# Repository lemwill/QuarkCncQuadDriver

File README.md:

# QuarkCnc

Inspired from:
https://github.com/Expatria-Technologies/grblhal_2000_PrintNC

https://github.com/grblHAL

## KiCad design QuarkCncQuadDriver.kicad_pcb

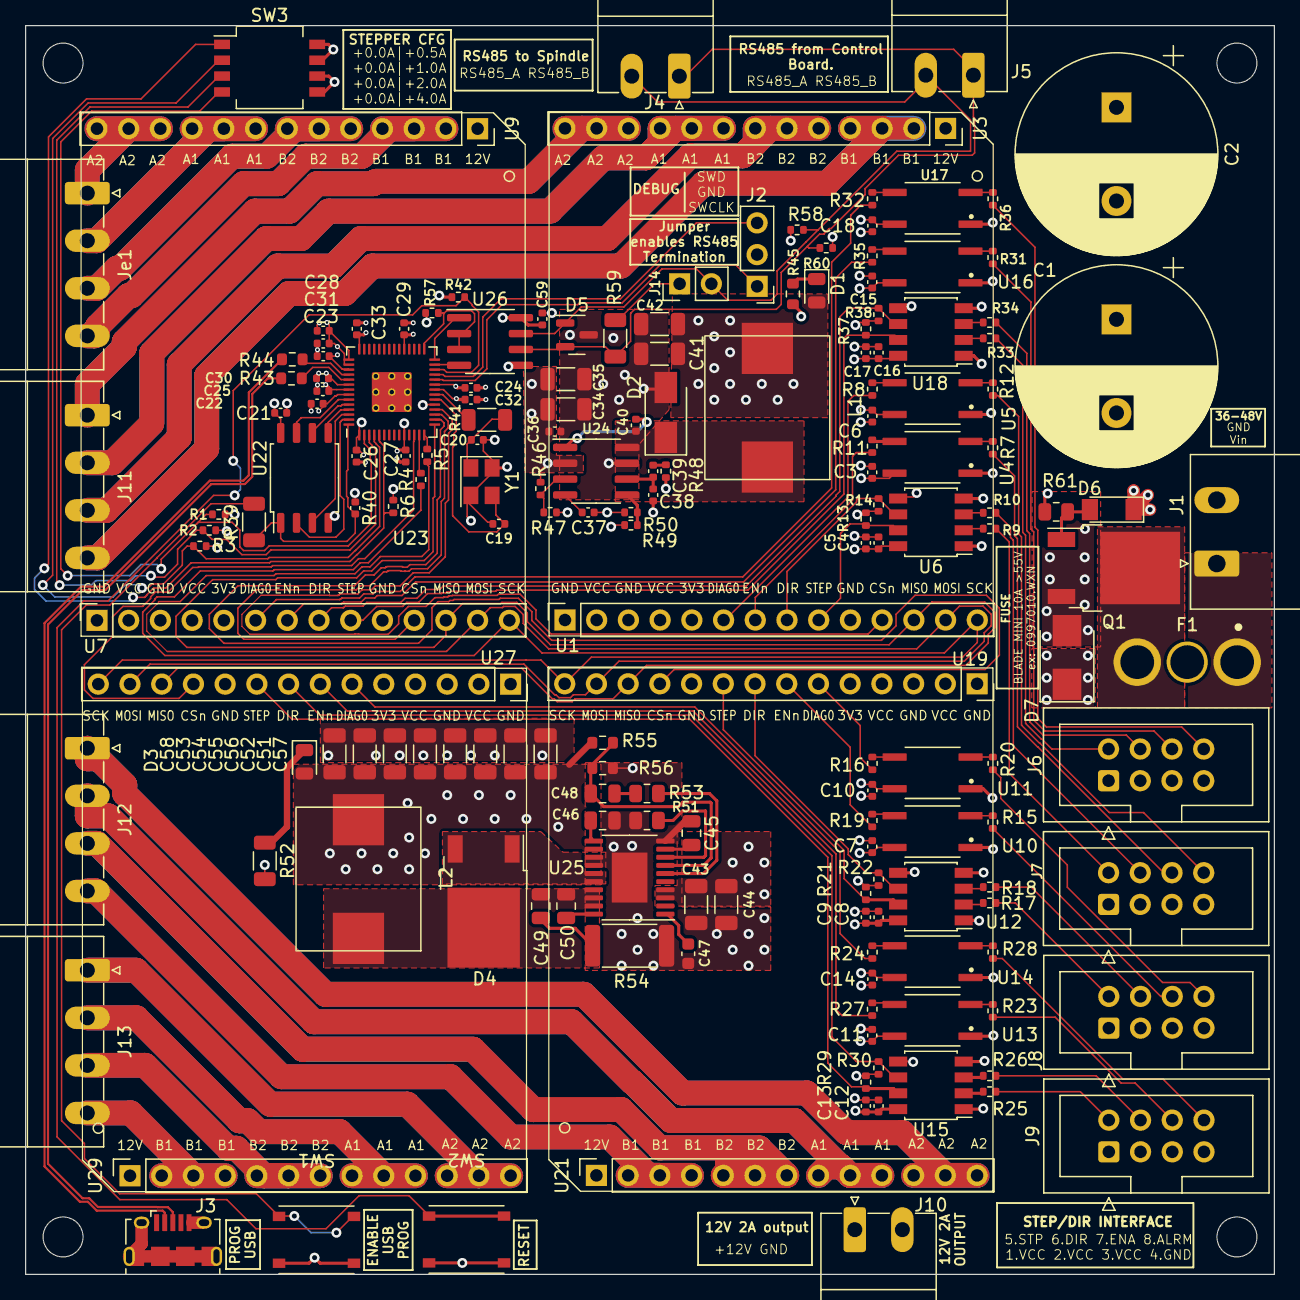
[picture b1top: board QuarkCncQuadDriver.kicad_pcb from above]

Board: 4 copper layers, 100.0 x 100.0 mm, 183 parts (0 on the bottom side), 137 nets.

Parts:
C1, C2: 1000uF; CP_Radial_D16.0mm_P7.50mm
C3, C7, C11, C15, C21, C22, C23, C25, C27, C28, C29, C30, C31, C32, C33, C40, C59: 100n 50V; C_0402_1005Metric
C4, C5, C6, C8, C9, C10, C12, C13, C14, C16, C17, C18: 100n; C_0402_1005Metric
C19, C20: 12p 50V; C_0402_1005Metric
C24, C26: 1u 25V; C_0402_1005Metric
C34, C35: 4.7uF 50V; C_1206_3216Metric
C36: 10nF 50V; C_0402_1005Metric
C37: 10nF; C_0402_1005Metric
C38: 47pF 50V; C_0402_1005Metric
C39: 1nF 50V; C_0402_1005Metric
C41, C42: 47uF 10V; C_1206_3216Metric
C43, C44: 2.2u 100V; C_1206_3216Metric
C45, C50: 330p 100V; C_0805_2012Metric
C46, C48: 10n 100V; C_0805_2012Metric
C47: 470n 25V; C_0603_1608Metric
C49: 22n 100V; C_0805_2012Metric
C51, C52, C53, C54, C55, C56, C57, C58: 22uF 25V; C_1206_3216Metric
D1, D3: RED LED; LED_0805_2012Metric
D2: D; D_SMA
D4: VS-6CWQ10FNTR-M3
D5: SM712_SOT23; SOT-23
D6: ZMM5V6; D_MiniMELF
D7: SMBJ51CA; D_SMB
F1: Fuse; Fuse_Littelfuse_178.6764.0001
H1, H2, H3, H4: MountingHole; MountingHole_3.2mm_M3_ISO7380
J1: Screw_Terminal_01x02; PhoenixContact_MSTBA_2,5_2-G-5,08_1x02_P5.08mm_Horizontal
J2: Conn_01x03_Male; PinHeader_1x03_P2.54mm_Vertical
J3: USB_B_Micro; USB_Micro-B_Amphenol_10118194_Horizontal
J4, J5, J10: Screw_Terminal_01x02; PhoenixContact_MC_1,5_2-G-3.81_1x02_P3.81mm_Horizontal
J6, J7, J8, J9: Conn_02x04_Odd_Even; IDC-Header_2x04_P2.54mm_Vertical
J11, J12, J13: Screw_Terminal_01x04; PhoenixContact_MC_1,5_4-G-3.81_1x04_P3.81mm_Horizontal
J14: Conn_01x02_Male; PinHeader_1x02_P2.54mm_Vertical
Je1: Screw_Terminal_01x04; PhoenixContact_MC_1,5_4-G-3.81_1x04_P3.81mm_Horizontal
L1, L2: MWSA1004S-330MT
Q1: WSF50P10; TO-252-2
R1, R2, R3, R6, R42, R49, R57: 10k; R_0402_1005Metric
R4, R5: 33; R_0402_1005Metric
R7, R8, R9, R10, R11, R12, R13, R14, R15, R16, R17, R18, R19, R20, R21, R22, R23, R24, R25, R26, R27, R28, R29, R30, R31, R32, R33, R34, R35, R36, R37, R38: 1K; R_0402_1005Metric
R39, R41, R52: 1k; R_1206_3216Metric
R40: DNI; C_0402_1005Metric
R43, R44: 27; R_0603_1608Metric
R45: 68R; R_0603_1608Metric
R46: 330k; R_0402_1005Metric
R47: 68k; R_0402_1005Metric
R48: 29.4k; R_0402_1005Metric
R50: 3.3k; R_0402_1005Metric
R51: 20k; R_0805_2012Metric
R53: 49.9k 1%; R_0805_2012Metric
R54: 10 1W; R_2512_6332Metric
R55: 9.1k; R_0603_1608Metric
R56: 1k; R_0603_1608Metric
R58, R60: DNI; R_0402_1005Metric
R59: 120 (DNI); R_1206_3216Metric
R61: 4.7k; R_0805_2012Metric
SW1, SW2: SW_DIP_x01; TS-1187A-B-A-B
SW3: SW_DIP_x04; SW_DIP_SPSTx04_Slide_XKB_DSHP04TS-S_W6.35mm_P1.27mm
U1, U7, U19, U27: StepperDriver_Conn2; PinSocket_1x14_P2.54mm_Vertical
U2, U8, U20, U28: StepperDriver; StepperDriverV3
U3, U9, U21, U29: StepperDriver_Conn1; PinSocket_1x13_P2.54mm_Vertical
U4, U5, U10, U11, U13, U14, U16, U17: EL357N-G; SOP254P700X200-4N
U6, U12, U15, U18: EL0631(TA); SSOP-8_3.95x5.21x3.27mm_P1.27mm
U22: W25Q128JVS; SOIC-8_5.23x5.23mm_P1.27mm
U23: RP2040; RP2040-QFN-56
U24: tps54331DR; SOIC-8_3.9x4.9mm_P1.27mm
U25: LM5576; HTSSOP-20-1EP_4.4x6.5mm_P0.65mm_EP2.85x4mm
U26: SP3485EN-L/TR; SOIC-8_3.9x4.9mm_P1.27mm
Y1: X322512MSB4SI; Crystal_SMD_3225-4Pin_3.2x2.5mm

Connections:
+3V3: C3.1, C4.1, C5.1, C6.1, C7.1, C8.1, C9.1, C10.1, C11.1, C12.1, C13.1, C14.1, C15.1, C16.1, C17.1, C18.1, C21.1, C25.1, C26.1, C27.1, C28.1, C29.1, C30.1, C31.1, C32.1, C33.1, C41.2, C42.2, C59.1, D1.2 (A), L1.2, R1.1, R2.1, R3.1, R6.1, R13.2, R14.2, R21.2, R22.2, R29.2, R30.2, R37.2, R38.2, R40.1, R42.2, R49.1, R60.1, U1.5 (3V3), U4.4, U5.4, U6.8 (VCC), U7.5 (3V3), U10.4, U11.4, U12.8 (VCC), U13.4, U14.4, U15.8 (VCC), U16.4, U17.4, U18.8 (VCC), U19.5 (3V3), U22.8 (VCC), U23.1 (IOVDD), U23.10 (IOVDD), U23.22 (IOVDD), U23.33 (IOVDD), U23.42 (IOVDD), U23.43 (ADC_AVDD), U23.44 (VREG_IN), U23.48 (USB_VDD), U23.49 (IOVDD), U26.8 (VCC), U27.5 (3V3)
+12V: C34.1, C35.1, C36.1, C51.1, C52.1, C53.1, C54.1, C55.1, C56.1, C57.1, C58.1, D3.2 (A), J10.1, L2.2, R46.1, R55.1, U3.1 (12V), U9.1 (12V), U21.1 (12V), U24.2 (VIN), U25.12 (OUT), U29.1 (12V)
/3.3V 1A Switching regulator/regulator_ph: C40.1, D2.1 (K), L1.1, U24.8 (PH)
/12V 3A Switching Regulator/lm5576_R60: C50.2, R54.1
/12V 3A Switching Regulator/lm5576_bst: C49.1, U25.20 (BST)
/12V 3A Switching Regulator/lm5576_is: D4.2 (A), U25.15 (IS), U25.16 (IS)
/12V 3A Switching Regulator/lm5576_sw: C49.2, C50.1, D4.1 (K), L2.1, U25.17 (SW), U25.18 (SW), U25.19 (PRE)
/Input_Protection/VCC_INPUT: F1.1, J1.1
/Input_Protection/reverse_polarity_protection: D6.2 (A), Q1.1 (G), R61.1
/Input_Protection/vcc_post_fuse: F1.2, Q1.2 (D)
/RP2040 Microcontroller/1V1: C22.1, C23.1, C24.1, U23.23 (DVDD), U23.45 (VREG_VOUT), U23.50 (DVDD)
/RP2040 Microcontroller/GPIO0: R1.2, SW3.4, U23.2 (GPIO0)
/RP2040 Microcontroller/GPIO1: R2.2, SW3.3, U23.3 (GPIO1)
/RP2040 Microcontroller/GPIO2: R3.2, SW3.2, U23.4 (GPIO2)
/RP2040 Microcontroller/GPIO3: R6.2, SW3.1, U23.5 (GPIO3)
/RP2040 Microcontroller/GPIO10: R4.2, U23.13 (GPIO10)
/RP2040 Microcontroller/GPIO11: R5.2, U23.14 (GPIO11)
/RP2040 Microcontroller/GPIO16: U23.27 (GPIO16), U26.4 (D)
/RP2040 Microcontroller/GPIO17: U23.28 (GPIO17), U26.1 (R)
/RP2040 Microcontroller/GPIO18: R57.2, U23.29 (GPIO18), U26.2 (~RE), U26.3 (DE)
/RP2040 Microcontroller/QSPI_SCLK: U22.6 (CLK), U23.52 (QSPI_SCLK)
/RP2040 Microcontroller/QSPI_SD0: U22.5 (DI(IO0)), U23.53 (QSPI_SD0)
/RP2040 Microcontroller/QSPI_SD1: U22.2 (DO(IO1)), U23.55 (QSPI_SD1)
/RP2040 Microcontroller/QSPI_SD2: U22.3 (IO2), U23.54 (QSPI_SD2)
/RP2040 Microcontroller/QSPI_SD3: U22.7 (IO3), U23.51 (QSPI_SD3)
/RP2040 Microcontroller/QSPI_SS: R39.1, R40.2, U22.1 (~CS), U23.56 (QSPI_SS)
/RP2040 Microcontroller/RUN: R42.1, SW2.2, U23.26 (RUN)
/RP2040 Microcontroller/SWCLK: J2.1, U23.24 (SWCLK)
/RP2040 Microcontroller/SWD: J2.3, U23.25 (SWD)
/RP2040 Microcontroller/USB_D+: J3.3 (D+), R43.1
/RP2040 Microcontroller/USB_D-: J3.2 (D-), R44.1
/RP2040 Microcontroller/XIN: C19.1, U23.20 (XIN), Y1.3
/RP2040 Microcontroller/XOUT: R41.1, U23.21 (XOUT)
/RP2040 Microcontroller/~USB_BOOT: R39.2, SW1.2
/RS485/RS485_A: D5.2 (A2), J4.1, J5.1, R59.1, R60.2, U26.6 (A)
/RS485/RS485_B: D5.1 (A1), J4.2, J5.2, J14.2, R58.1, U26.7 (B)
/STEPPER DRIVER A/STEPPER_COIL_A1: J13.2, U29.8 (A1), U29.9 (A1), U29.10 (A1)
/STEPPER DRIVER A/STEPPER_COIL_A2: J13.1, U29.11 (A2), U29.12 (A2), U29.13 (A2)
/STEPPER DRIVER A/STEPPER_COIL_B1: J13.4, U29.2 (B1), U29.3 (B1), U29.4 (B1)
/STEPPER DRIVER A/STEPPER_COIL_B2: J13.3, U29.5 (B2), U29.6 (B2), U29.7 (B2)
/STEPPER DRIVER X/STEPPER_COIL_A1: Je1.2, U9.8 (A1), U9.9 (A1), U9.10 (A1)
/STEPPER DRIVER X/STEPPER_COIL_A2: Je1.1, U9.11 (A2), U9.12 (A2), U9.13 (A2)
/STEPPER DRIVER X/STEPPER_COIL_B1: Je1.4, U9.2 (B1), U9.3 (B1), U9.4 (B1)
/STEPPER DRIVER X/STEPPER_COIL_B2: Je1.3, U9.5 (B2), U9.6 (B2), U9.7 (B2)
/STEPPER DRIVER Y/STEPPER_COIL_A1: J11.2, U3.8 (A1), U3.9 (A1), U3.10 (A1)
/STEPPER DRIVER Y/STEPPER_COIL_A2: J11.1, U3.11 (A2), U3.12 (A2), U3.13 (A2)
/STEPPER DRIVER Y/STEPPER_COIL_B1: J11.4, U3.2 (B1), U3.3 (B1), U3.4 (B1)
/STEPPER DRIVER Y/STEPPER_COIL_B2: J11.3, U3.5 (B2), U3.6 (B2), U3.7 (B2)
/STEPPER DRIVER Z/STEPPER_COIL_A1: J12.2, U21.8 (A1), U21.9 (A1), U21.10 (A1)
/STEPPER DRIVER Z/STEPPER_COIL_A2: J12.1, U21.11 (A2), U21.12 (A2), U21.13 (A2)
/STEPPER DRIVER Z/STEPPER_COIL_B1: J12.4, U21.2 (B1), U21.3 (B1), U21.4 (B1)
/STEPPER DRIVER Z/STEPPER_COIL_B2: J12.3, U21.5 (B2), U21.6 (B2), U21.7 (B2)
/STEPPER_A_CSn: U23.12 (GPIO9), U27.11 (SPI_CSn)
/STEPPER_A_DIAG0: R24.2, U27.6 (DIAG0)
/STEPPER_A_DIR: R30.1, U15.6 (VO2), U27.8 (STEPPER_DIR)
/STEPPER_A_ENn: R27.1, U27.7 (STEPPER_ENn)
/STEPPER_A_STEP: R29.1, U15.7 (VO1), U27.9 (STEPPER_STEP)
/STEPPER_MISO: U1.12 (SPI_MISO), U7.12 (SPI_MISO), U19.12 (SPI_MISO), U23.15 (GPIO12), U27.12 (SPI_MISO)
/STEPPER_MOSI: R5.1, U1.13 (SPI_MOSI), U7.13 (SPI_MOSI), U19.13 (SPI_MOSI), U27.13 (SPI_MOSI)
/STEPPER_SCK: R4.1, U1.14 (SPI_SCK), U7.14 (SPI_SCK), U19.14 (SPI_SCK), U27.14 (SPI_SCK)
/STEPPER_X_CSn: U7.11 (SPI_CSn), U23.17 (GPIO14)
/STEPPER_X_DIAG0: R32.2, U7.6 (DIAG0)
/STEPPER_X_DIR: R38.1, U7.8 (STEPPER_DIR), U18.6 (VO2)
/STEPPER_X_ENn: R35.1, U7.7 (STEPPER_ENn)
/STEPPER_X_STEP: R37.1, U7.9 (STEPPER_STEP), U18.7 (VO1)
/STEPPER_Y_CSn: U1.11 (SPI_CSn), U23.18 (GPIO15)
/STEPPER_Y_DIAG0: R8.2, U1.6 (DIAG0)
/STEPPER_Y_DIR: R14.1, U1.8 (STEPPER_DIR), U6.6 (VO2)
/STEPPER_Y_ENn: R11.1, U1.7 (STEPPER_ENn)
/STEPPER_Y_STEP: R13.1, U1.9 (STEPPER_STEP), U6.7 (VO1)
/STEPPER_Z_CSn: U19.11 (SPI_CSn), U23.16 (GPIO13)
/STEPPER_Z_DIAG0: R16.2, U19.6 (DIAG0)
/STEPPER_Z_DIR: R22.1, U12.6 (VO2), U19.8 (STEPPER_DIR)
/STEPPER_Z_ENn: R19.1, U19.7 (STEPPER_ENn)
/STEPPER_Z_STEP: R21.1, U12.7 (VO1), U19.9 (STEPPER_STEP)
/Stepper Isolation 1/alarm_ext: J6.8, R36.2
/Stepper Isolation 1/dir_ext: J6.4, R34.1
/Stepper Isolation 1/ena_ext: J6.6, R31.1
/Stepper Isolation 1/ena_ext_opto: R31.2, U16.2
/Stepper Isolation 1/step_ext: J6.2, R33.1
/Stepper Isolation 2/alarm_ext: J7.8, R12.2
/Stepper Isolation 2/dir_ext: J7.4, R10.1
/Stepper Isolation 2/ena_ext: J7.6, R7.1
/Stepper Isolation 2/ena_ext_opto: R7.2, U4.2
/Stepper Isolation 2/step_ext: J7.2, R9.1
/Stepper Isolation 3/alarm_ext: J8.8, R20.2
/Stepper Isolation 3/dir_ext: J8.4, R18.1
/Stepper Isolation 3/ena_ext: J8.6, R15.1
/Stepper Isolation 3/ena_ext_opto: R15.2, U10.2
/Stepper Isolation 3/step_ext: J8.2, R17.1
/Stepper Isolation 4/alarm_ext: J9.8, R28.2
/Stepper Isolation 4/dir_ext: J9.4, R26.1
/Stepper Isolation 4/ena_ext: J9.6, R23.1
/Stepper Isolation 4/ena_ext_opto: R23.2, U13.2
/Stepper Isolation 4/step_ext: J9.2, R25.1
GND: C1.2, C2.2, C3.2, C4.2, C5.2, C6.2, C7.2, C8.2, C9.2, C10.2, C11.2, C12.2, C13.2, C14.2, C15.2, C16.2, C17.2, C18.2, C19.2, C20.2, C21.2, C22.2, C23.2, C24.2, C25.2, C26.2, C27.2, C28.2, C29.2, C30.2, C31.2, C32.2, C33.2, C34.2, C35.2, C36.2, C37.2, C38.2, C41.1, C42.1, C43.2, C44.2, C45.2, C46.2, C47.2, C51.2, C52.2, C53.2, C54.2, C55.2, C56.2, C57.2, C58.2, C59.2, D2.2 (A), D5.3 (common), D7.1 (A1), J1.2, J2.2, J3.5 (GND), J3.6 (Shield), J10.2, R45.2, R47.2, R48.2, R50.2, R51.2, R52.2, R54.2, R56.2, R57.1, R58.2, R61.2, SW1.1, SW2.1, SW3.5, SW3.6, SW3.7, SW3.8, U1.1 (GND), U1.3 (GND), U1.10 (GND), U6.5 (GND), U7.1 (GND), U7.3 (GND), U7.10 (GND), U12.5 (GND), U15.5 (GND), U18.5 (GND), U19.1 (GND), U19.3 (GND), U19.10 (GND), U22.4 (GND), U23.19 (TESTEN), U23.57 (GND), U24.7 (GND), U25.10 (AGND), U25.13 (PGND), U25.14 (PGND), U25.21 (EP), U26.5 (GND), U27.1 (GND), U27.3 (GND), U27.10 (GND), Y1.2, Y1.4
unnamed: C20.1, R41.2, Y1.1
unnamed: C37.1, U24.4 (SS)
unnamed: C38.1, C39.1, U24.6 (COMP)
unnamed: C39.2, R48.1
unnamed: C40.2, U24.1 (BOOT)
unnamed: C45.1, U25.9 (RAMP)
unnamed: C46.1, U25.11 (SS)
unnamed: C47.1, U25.1 (VCC)
unnamed: C48.1, R55.2, R56.1, U25.7 (FB)
unnamed: C48.2, R53.1
unnamed: D1.1 (K), R45.1
unnamed: D3.1 (K), R52.1
unnamed: J14.1, R59.2
unnamed: R8.1, U5.3
unnamed: R9.2, U6.2 (C1)
unnamed: R10.2, U6.3 (C2)
unnamed: R11.2, U4.3
unnamed: R12.1, U5.2
unnamed: R16.1, U11.3
unnamed: R17.2, U12.2 (C1)
unnamed: R18.2, U12.3 (C2)
unnamed: R19.2, U10.3
unnamed: R20.1, U11.2
unnamed: R24.1, U14.3
unnamed: R25.2, U15.2 (C1)
unnamed: R26.2, U15.3 (C2)
unnamed: R27.2, U13.3
unnamed: R28.1, U14.2
unnamed: R32.1, U17.3
unnamed: R33.2, U18.2 (C1)
unnamed: R34.2, U18.3 (C2)
unnamed: R35.2, U16.3
unnamed: R36.1, U17.2
unnamed: R43.2, U23.47 (USB_DP)
unnamed: R44.2, U23.46 (USB_DM)
unnamed: R46.2, R47.1, U24.3 (EN)
unnamed: R49.2, R50.1, U24.5 (VSENS)
unnamed: R51.1, U25.8 (RT)
unnamed: R53.2, U25.6 (COMP)
VCC: C1.1, C2.1, C43.1, C44.1, D6.1 (K), D7.2 (A2), Q1.3 (D), U1.2 (VCC), U1.4 (VCC), U7.2 (VCC), U7.4 (VCC), U19.2 (VCC), U19.4 (VCC), U25.3 (VIN), U25.4 (VIN), U27.2 (VCC), U27.4 (VCC)
VCC_EXT: J6.1, J6.3, J6.5, J7.1, J7.3, J7.5, J8.1, J8.3, J8.5, J9.1, J9.3, J9.5, U4.1, U5.1, U6.1 (A1), U6.4 (A2), U10.1, U11.1, U12.1 (A1), U12.4 (A2), U13.1, U14.1, U15.1 (A1), U15.4 (A2), U16.1, U17.1, U18.1 (A1), U18.4 (A2)

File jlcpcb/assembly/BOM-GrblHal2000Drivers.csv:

Comment,Designator,Footprint,LCSC
10n 100V,"C45,C47",C_0805_2012Metric,C107135
22n 100V,C48,C_0805_2012Metric,C107137
330p 100V,"C44,C49",C_0805_2012Metric,C113820
1K,"R10,R11,R12,R13,R14,R15,R16,R17,R18,R19,R20,R21,R22,R23,R24,R25,R26,R27,R28,R29,R30,R31,R32,R33,R34,R35,R36,R37,R38,R7,R8,R9",R_0402_1005Metric,C11702
StepperDriver_Conn2,"U1,U19,U21,U27,U29,U3,U7,U9",PinSocket_1x14_P2.54mm_Vertical,C124407
22uF 25V,"C50,C51,C52,C53,C54,C55,C56,C57",C_1206_3216Metric,C12891
USB_B_Micro,J3,USB_Micro-B_Amphenol_10118194_Horizontal,C132563
Fuse,F1,Fuse_Littelfuse_178.6764.0001,C142933
SMBJ51CA,D7,D_SMB,C151265
10nF 50V,"C35,C36",C_0402_1005Metric,C15195
1nF 50V,C38,C_0402_1005Metric,C1523
12p 50V,"C19,C20",C_0402_1005Metric,C1547
47pF 50V,C37,C_0402_1005Metric,C1567
470n 25V,C46,C_0603_1608Metric,C1623
2.2u 100V,"C42,C43",C_1206_3216Metric,C170101
4.7k,R61,R_0805_2012Metric,C17673
49.9k 1%,R53,R_0805_2012Metric,C17719
RP2040,U23,RP2040-QFN-56,C2040
1k,R56,R_0603_1608Metric,C21190
D,D2,D_SMA,C22452
29.4k,R48,R_0402_1005Metric,C226949
9.1k,R55,R_0603_1608Metric,C23260
33,"R4,R5",R_0402_1005Metric,C25105
27,"R43,R44",R_0603_1608Metric,C25190
10k,"R1,R2,R3,R42,R49,R57,R6",R_0402_1005Metric,C25744
330k,R46,R_0402_1005Metric,C25778
3.3k,R50,R_0402_1005Metric,C25890
WSF50P10,Q1,TO-252-2,C2758447
68R,R45,R_0603_1608Metric,C27592
4.7uF 50V,"C33,C34",C_1206_3216Metric,C29823
100n,"C10,C11,C12,C13,C14,C15,C16,C17,C18,C21,C22,C23,C25,C27,C28,C29,C3,C30,C31,C32,C39,C4,C5,C58,C6,C7,C8,C9",C_0402_1005Metric,C307331
SW_DIP_x01,"SW1,SW2",TS-1187A-B-A-B,C318884
SM712_SOT23,D5,SOT-23,C32677
68k,R47,R_0402_1005Metric,C36871
SW_DIP_x04,SW3,SW_DIP_SPSTx04_Slide_Omron_A6H-4101_W6.15mm_P1.27mm,C397291
MWSA1206S-330MT,"L1,L2",MWSA1004S-330MT,C408490
20k,R51,R_0805_2012Metric,C4328
1k,"R39,R41,R52",R_1206_3216Metric,C4410
EL0631(TA),"U12,U15,U18,U6",SSOP-8_3.95x5.21x3.27mm_P1.27mm,C465944
VS-6CWQ10FNTR-M3,D4,VS-6CWQ10FNTR-M3,C468124
10 1W,R54,R_2512_6332Metric,C47019
1000uF,"C1,C2",CP_Radial_D16.0mm_P7.50mm,C47881
Conn_01x02_Male,J14,PinHeader_1x02_P2.54mm_Vertical,C492401
1u 25V,"C24,C26",C_0402_1005Metric,C52923
LM5576,U25,HTSSOP-20-1EP_4.4x6.5mm_P0.65mm_EP2.85x4mm,C62562
EL357N-G,"U10,U11,U13,U14,U16,U17,U4,U5",SOP254P700X200-4N,C6649
Screw_Terminal_01x04,"J11,J12,J13,Je1","PhoenixContact_MC_1,5_4-G-3.81_1x04_P3.81mm_Horizontal",C7245
ZMM5V6,D6,D_MiniMELF,C8062
Screw_Terminal_01x02,"J1,J10,J4,J5","PhoenixContact_MC_1,5_2-G-3.81_1x02_P3.81mm_Horizontal",C8387
RED LED,"D1,D3",LED_0805_2012Metric,C84256
SP3485EN-L/TR,U26,SOIC-8_3.9x4.9mm_P1.27mm,C8963
X322512MSB4SI,Y1,Crystal_SMD_3225-4Pin_3.2x2.5mm,C9002
Conn_02x04_Odd_Even,"J6,J7,J8,J9",IDC-Header_2x04_P2.54mm_Vertical,C9135
47uF 10V,"C40,C41",C_1206_3216Metric,C96123
W25Q128JVS,U22,SOIC-8_5.23x5.23mm_P1.27mm,C97521
tps54331DR,U24,SOIC-8_3.9x4.9mm_P1.27mm,C9865
StepperDriver,U8,StepperDriverV2,
DNI,R40,C_0402_1005Metric,
120 (DNI),R59,R_1206_3216Metric,
MountingHole,H3,MountingHole_3.2mm_M3_ISO7380,
Conn_01x03_Male,J2,PinHeader_1x03_P2.54mm_Vertical,
DNI,R60,R_0402_1005Metric,
StepperDriver,U28,StepperDriverV2,
StepperDriver,U2,StepperDriverV2,
MountingHole,H1,MountingHole_3.2mm_M3_ISO7380,
StepperDriver,U20,StepperDriverV2,
MountingHole,H2,MountingHole_3.2mm_M3_ISO7380,
MountingHole,H4,MountingHole_3.2mm_M3_ISO7380,
DNI,R58,R_0402_1005Metric,

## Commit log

2022-08-23 Added MFG files
2022-08-23 Added assembly files
2022-09-04 Fixed reset/boot button footprint
2022-09-21 Keyed stepper drivers. Larger input connector
2023-05-20 Add schematic PDF
